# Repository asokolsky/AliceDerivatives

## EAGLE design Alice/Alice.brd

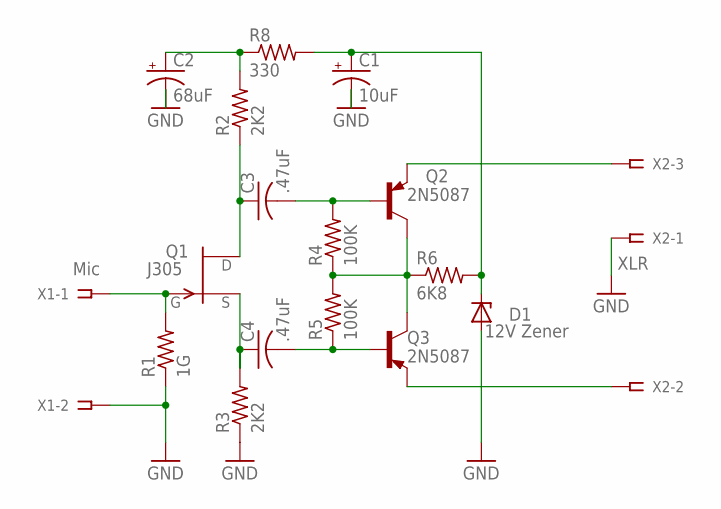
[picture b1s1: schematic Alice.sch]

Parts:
C1: 10uF; E1,8-4
C2: 68uF; E3,5-10
C3, C4: .47uF; C075-052X106
D1: 12V Zener; DO35Z10
Q1: J305; TO-92
Q2, Q3: 2N5087; TO92-EBC-OVAL
R1: 1G; 0204/7
R2, R3: 2K2; 0204/7
R4, R5: 100K; 0204/7
R6: 6K8; 0204/7
R8: 330; 0204/7
X1: Mic; SSW-101-02-S-D
X2: XLR; SSW-101-02-S-T

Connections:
unnamed: C3.1, Q1.3 (D), R2.1
unnamed: Q2.E, X2.3
unnamed: C2.+, R2.2, R8.1
unnamed: C4.1, Q1.2 (S), R3.2
unnamed: Q2.C, Q3.C, R4.1, R5.2, R6.1
unnamed: C3.2, Q2.B, R4.2
unnamed: C4.2, Q3.B, R5.1
unnamed: Q1.1 (G), R1.2, X1.1
unnamed: C1.+, D1.C, R6.2, R8.2
unnamed: Q3.E, X2.2
XLR-1: C1.-, C2.-, D1.A, R1.1, R3.1, X1.2, X2.1

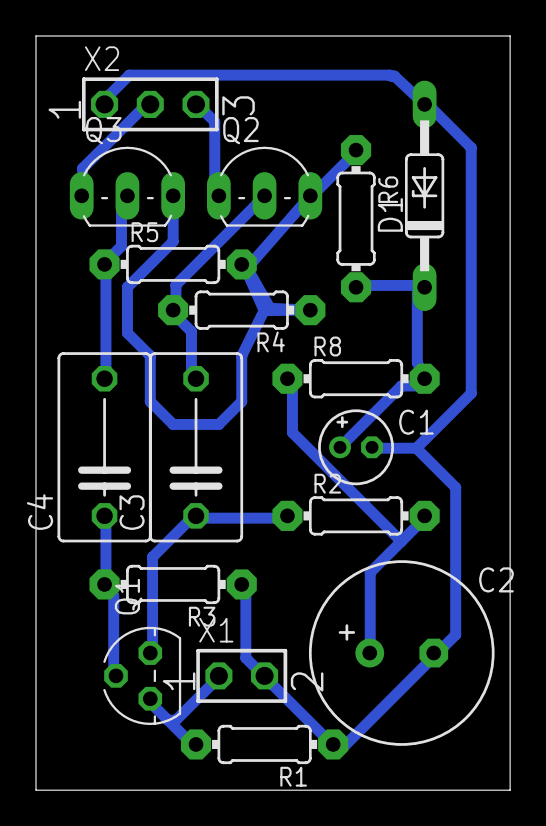
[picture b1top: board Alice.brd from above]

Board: 2 copper layers, 26.3 x 41.9 mm, 17 parts (0 on the bottom side), 11 nets.

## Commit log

2015-10-17 :circus_tent: Added .gitattributes & .gitignore files
2015-10-17 First commit
    Alice condenser microphone and its relatives.
2016-07-13 Done!
